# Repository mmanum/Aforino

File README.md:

# Aforino
## A Arduino and ESP8266  Project. Capacity monitor.

Afonio is a Arduino and ESP8266 Project. New use this platforms and we monitor the capacity of a local.

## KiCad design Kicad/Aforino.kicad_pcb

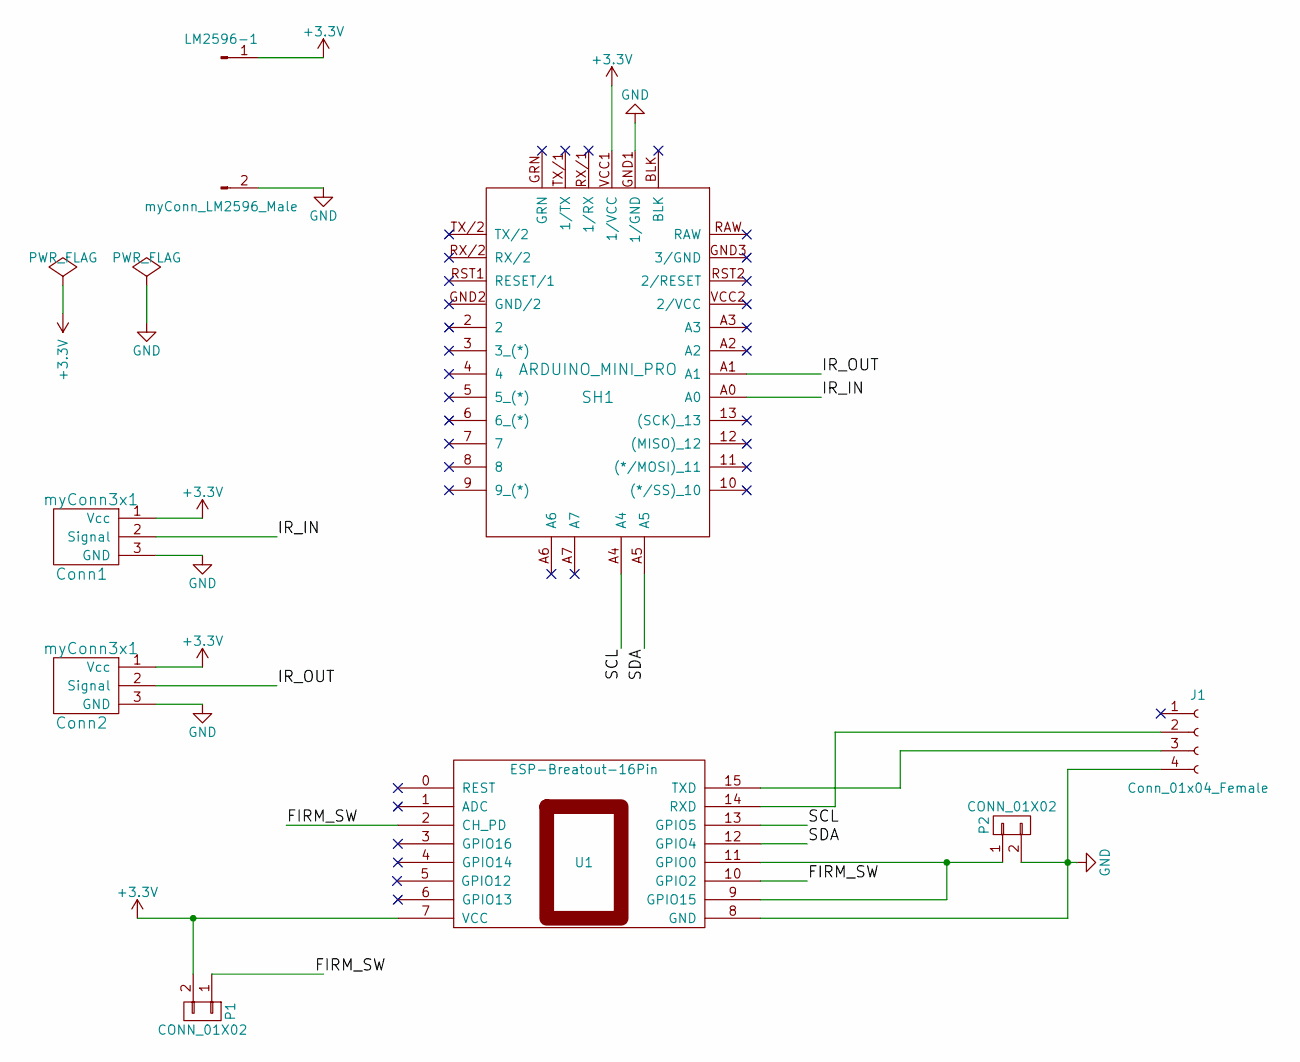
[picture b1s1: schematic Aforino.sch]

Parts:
Conn1, Conn2: myConn3x1; MyConn3x1
J1: Conn_01x04_Female; PinHeader_1x04_P2.54mm_Vertical
LM2596-1: myConn_LM2596_Male
P1, P2: CONN_01X02; Pin_Header_Straight_1x02
SH1: ARDUINO_MINI_PRO; ARDUINO_MINI_PRO_V10
U1: ESP-Breatout-16Pin; ESP8266-Breakout_Board-16Pin

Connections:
+3V3: Conn1.1 (Vcc), Conn2.1 (Vcc), LM2596-1.1, P1.2, SH1.VCC1 (1/VCC), U1.7 (VCC)
/FIRM_SW: P1.1, U1.2 (CH_PD), U1.10 (GPIO2)
/IR_IN: Conn1.2 (Signal), SH1.A0
/IR_OUT: Conn2.2 (Signal), SH1.A1
/SCL: SH1.A4, U1.13 (GPIO5)
/SDA: SH1.A5, U1.12 (GPIO4)
GND: Conn1.3 (GND), Conn2.3 (GND), J1.4, LM2596-1.2, P2.2, SH1.GND1 (1/GND), U1.8 (GND)
unnamed: J1.2, U1.14 (RXD)
unnamed: J1.3, U1.15 (TXD)
unnamed: P2.1, U1.9 (GPIO15), U1.11 (GPIO0)

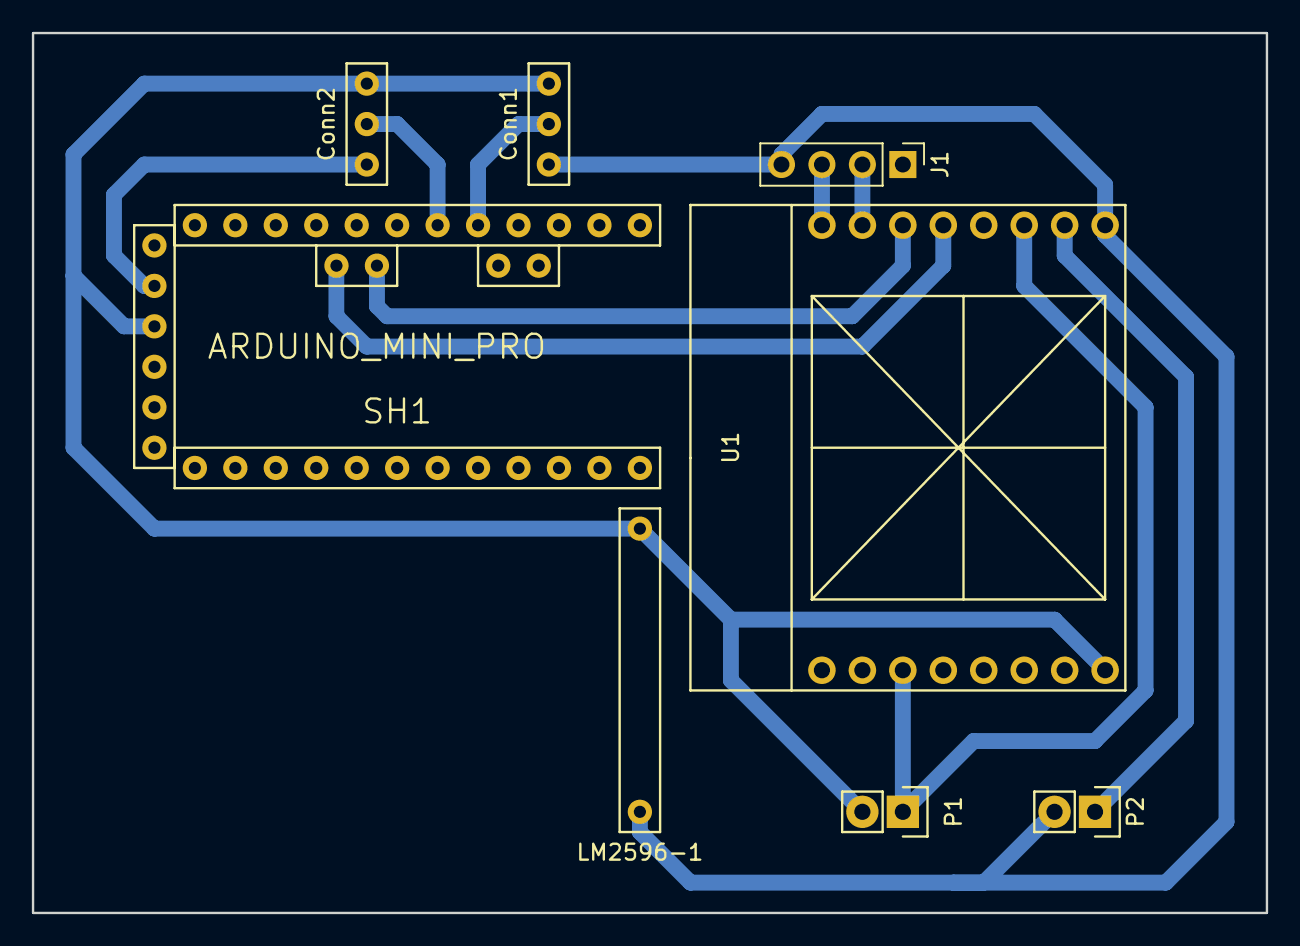
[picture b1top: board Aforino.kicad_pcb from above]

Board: 2 copper layers, 77.5 x 55.2 mm, 8 parts (0 on the bottom side), 10 nets.

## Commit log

2018-01-19 Inicialización del Proyecto. Arduino Platformio + Kicad Project and libraries
2018-01-20 Under Contruction: Kicad
2018-01-21 Under Contruction: Kicad Pcbnew, Track and Vias
2018-01-30 Kidcat first testing board
2018-02-22 Kicad: SVG v1 Logo Escolabs
2018-03-12 Kicad: ESP8266 Breakout Shield Good! Jumpers to Upload firmware! Best component order!
